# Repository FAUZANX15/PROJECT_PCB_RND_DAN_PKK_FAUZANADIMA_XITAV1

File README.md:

# PROJECT_PCB_RND_DAN_PKK_FAUZANADIMA_XITAV1

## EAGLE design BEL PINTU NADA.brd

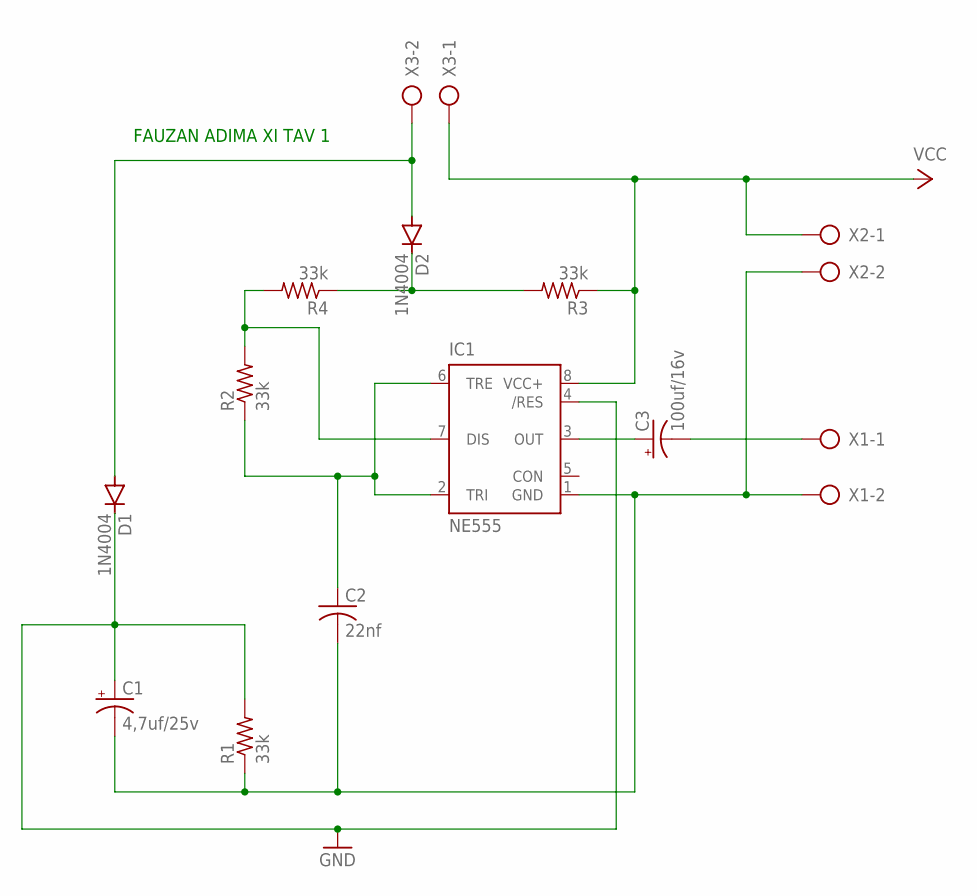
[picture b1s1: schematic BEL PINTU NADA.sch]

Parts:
C1: 4,7uf/25v; E2-4
C2: 22nf; C025-025X050
C3: 100uf/16v; E2-4
D1, D2: 1N4004; DO41-10
IC1: NE555; DIL-08
R1, R2, R3, R4: 33k; 0309/12
X1, X2, X3: AK300/2

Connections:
GND: C1.+, D1.C, IC1.4 (/RES), R1.2
unnamed: C3.+, IC1.3 (OUT)
unnamed: C3.-, X1.1
unnamed: C1.-, C2.2, IC1.1 (GND), R1.1, X1.2, X2.2
unnamed: D2.C, R3.2, R4.1
unnamed: D1.A, D2.A, X3.2
unnamed: IC1.7 (DIS), R2.2, R4.2
unnamed: C2.1, IC1.2 (TRI), IC1.6 (TRE), R2.1
VCC: IC1.8 (VCC+), R3.1, X2.1, X3.1

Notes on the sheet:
FAUZAN ADIMA XI TAV 1

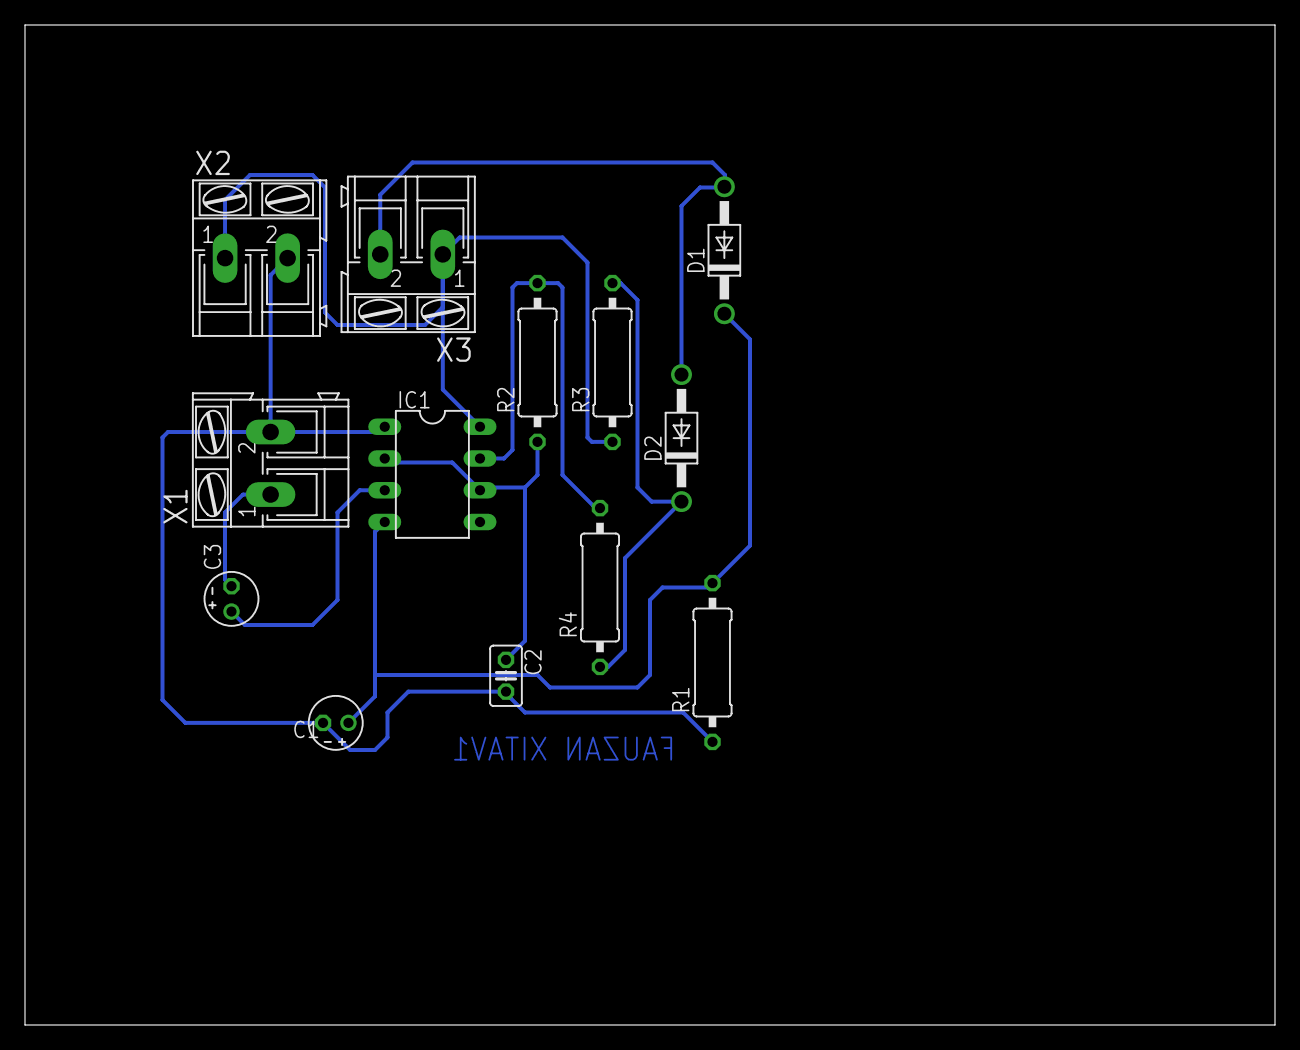
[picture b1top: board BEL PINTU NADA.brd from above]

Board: 2 copper layers, 100.0 x 80.0 mm, 13 parts (0 on the bottom side), 9 nets.

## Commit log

2025-02-08 BEL PINTU DUA NADA FAUZAN ADIMA SCHEMATIC XI TAV 1
2025-02-08 FLIP-FLOP FAUZAN ADIMA XI TAV 1
